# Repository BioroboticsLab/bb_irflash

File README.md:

# bb_irflash - Infrared LED flashing software and hardware

----
## What is bb_irflash?

bb_irflash is a software and hardware layout package. It contains the circuit and board layout for creating infrared flashing devices.

## Software

The software is C code written and tested for the Arduino Board Duemilanove. However, it should be easily adjusted to fit any arduino available on the market.

## Hardware

The hardware is designed to be triggered via signal current and powered with 12V. The design contains no protection mechanism whatsoever. So exchanging the resistors and/or LED's enables faster/slower flashing or constant lighting. 

The board dimensions are 23mmx51mm, single sided layout. Parts as described in the 'Parts' section enable flashing at 3 Hz and 20 ms duration. Designs come in EAGLE format.

# Parts

## SMD Parts Required for the Boards

The following Surface-Mount Device (SMD) parts are required for the boards:

### MOSFETs
- 8x [NTMS4807NR2G 'AO4752'](https://www.mouser.de/ProductDetail/863-NTMS4807NR2G)

### LEDs
- 8x [LED OSRAM 'SFH 4716AS A01'](https://www.mouser.de/ProductDetail/ams-OSRAM/SFH-4716AS-A01?qs=%252BEew9%252B0nqrDXvNyoSKrong%3D%3D)

### Signal Amplifiers
- 4x [Signal Amplifier 'LM358LVIDR'](https://www.mouser.de/ProductDetail/595-LM358LVIDR)

### Resistors
- 32x [2 Ohm Resistor '603-RC2512JK-072RL'](https://www.mouser.de/ProductDetail/603-RC2512JK-072RL)
- 16x [10k Ohm Resistor '71-CRCW060310K0JNEAC'](https://www.mouser.de/ProductDetail/71-CRCW060310K0JNEAC)
- 2x [4.7k Ohm Resistor '71-CRCW06034K70JNEAC'](https://www.mouser.de/ProductDetail/71-CRCW06034K70JNEAC)
- 4x [22k Ohm Resistor '71-CRCW060322K0JNEAC'](https://www.mouser.de/ProductDetail/71-CRCW060322K0JNEAC)
- 1x [20k Ohm Resistor 'R0603'](Beta Layout standard part) [20k Resistor on Mouser '71-CRCW060320K0JNEA'](https://www.mouser.de/ProductDetail/71-CRCW060320K0JNEAC)
)
- 1x [100k Ohm Resistor '71-CRCW0603100KFKEAC'](https://www.mouser.de/ProductDetail/71-CRCW0603100KFKEAC)

### Capacitors
- 4x [0.01uF Capacitor '810-C1005X7R1H103KBE'](https://www.mouser.de/ProductDetail/810-C1005X7R1H103KBE)
- 2x [1uF Capacitor '81-GRM155R61C105MA2D'](https://www.mouser.de/ProductDetail/81-GRM155R61C105MA2D)

### Diodes
- 2x [Schottky Diode 'CDBU0230R-HF'](https://www.mouser.de/ProductDetail/750-CDBU0230R-HF)

### Transistors
- 2x [NPN Transistor 'NSVMMBT2222AM3T5G'](https://www.mouser.de/ProductDetail/863-NSVMMBT2222AM3T5)

### Timer
- 2x [Timer 'NE555DR'](https://www.mouser.de/ProductDetail/595-NE555DR)

### Logic Gates
- 1x [Dual AND Gate '74LVC2G08'](https://www.mouser.de/ProductDetail/771-74LVC2G08DP-G)

## Through-hole-technology (THT) required components to solder on

### Capacitors
- 8x [2mF Capacitor '667-EEU-FP1E202B'](https://www.mouser.de/ProductDetail/667-EEU-FP1E202B)

### MOSFET
- 1x [STD12NF06L-1 'STD12NF06L-1'](https://www.mouser.de/ProductDetail/511-STD12NF06L-1)

### Connectors
- 8x [Header - Board to LED connections](https://www.mouser.de/ProductDetail/538-43045-0400)
- 1x [Header - Arduino connection](https://www.mouser.de/ProductDetail/538-105313-1203).  Note that the picture shows the incorrect part with number 1103.  The right angle connection
- 1x [Header - Power supply connection](https://www.mouser.de/ProductDetail/538-76825-0002)

See order_examples for further detail, and reference the picture for needed parts.  

# Mouser project order templates for parts:
- [bb_irflash SMD components Mouser project to order](https://eu.mouser.com/ProjectManager/ProjectDetail.aspx?AccessID=517e59b65d)
- [bb_irflash SMD components spreadsheet list](order_examples/BB_IRFLASH_SMD_COMPONENTS.xls)
- [bb_irflash THT components Mouser project to order](https://eu.mouser.com/ProjectManager/ProjectDetail.aspx?AccessID=0B309C354D)
- [bb_irflash THT components spreadsheet list](order_examples/BB_IRFLASH_THT_COMPONENTS.xls)
- [Cables for connecting lights, Arduino, and power supply](https://www.mouser.de/ProjectManager/ProjectDetail.aspx?AccessID=e691302b18). Note that the Arduino connection cable (Nanofit) and the power supply cable (Megafit) connect to the board, but will have to be cut/adjusted to make appropriate connections to the Arduino/power supply

# Power supply
The board is typically driven at 5V.  However, higher light output can be achieved by driving at slightly higher voltages.  here are suitable power supply for these voltages.  Note that when operating at 6fps and 5msec flashes, one board will draw 1-1.5 amps maximum.  Therefore one of these power supplies is sufficient to drive multiple boards.
- [5V power supply (adjustable in range 4.75-5.8V)](https://www.mouser.de/ProductDetail/MEAN-WELL/HRP-100-5?qs=Pc4kzEvJlcQLHIPhYtoJzw%3D%3D)
- [7.5V power supply (adjustable in range 6-9V)](https://www.mouser.de/ProductDetail/MEAN-WELL/RSP-320-7.5?qs=Uzd%2Fwh%252BZzhAvdwoq1II01Q%3D%3D).  Also available at [Conrad](https://www.conrad.de/de/p/mean-well-rsp-320-7-5-schaltnetzteil-7-5-v-dc-40-a-300-w-2249344.html?utm_source=google&utm_medium=cpc&utm_campaign=GB1_Messtechnik+%26+Stromversorgung_Generic&utm_id=43483581&gad_source=1&gbraid=0AAAAAD1-3H5RXiWIoMa0wxSd_K8oRlJKH&gclid=CjwKCAiAudG5BhAREiwAWMlSjDPmVMJK24BTLvHd9yjfUtIwc8q5r0EybappmSUyCZYAYHu7tNM5choC1wwQAvD_BwE&refresh=true)

# Board V2.0

The new IR flash board have the exact same performance as the previous version. The only new part is a better connectivity and a protection circuit.
The protection circuit is limiting the impulse duration to 20ms with a pause of 100ms between each pulse for protecting the LED. The power supply should be 
V ; 6A. To use it just send a step signal of the wanted duration to the trigger pin of the board (The step signal should not be wider than 20ms high and a pause of 100ms should be observe between each pulse)

The files in "board_V2" folder are all the project file in KiCAD format. If you have no interest in redesign, they are not interesting for you. 

For fabrication you only need the files in the fabrication folder.
The gerber files contained in "fabrication/gerber" are the map of your circuits - You manufacturer would ask for them (likely as a zip file, i.e. gerber.zip containing all folder contents).  The subfolder : "fabrication/gerber/drill_file" contain the coordinate of all the holes drilled into the board.

If you want to ask a third party for assembly, you will need the gerber files, the components position files ("Bestückungsplan": assembly_map_top.pdf
and assembly_map_bottom.pdf), the Pick&Place placement file (Pick&Place.txt), and the components list (Bill of Materials: BOM.xlsx). The 
The components position files are in component_position folder (Bottom and top layer). Note that the BOM format can vary in function of your third party company.

The folder order_examples contains two examples for orders placed through Beta Layout with components ordered through Mouser.  These are for reference.

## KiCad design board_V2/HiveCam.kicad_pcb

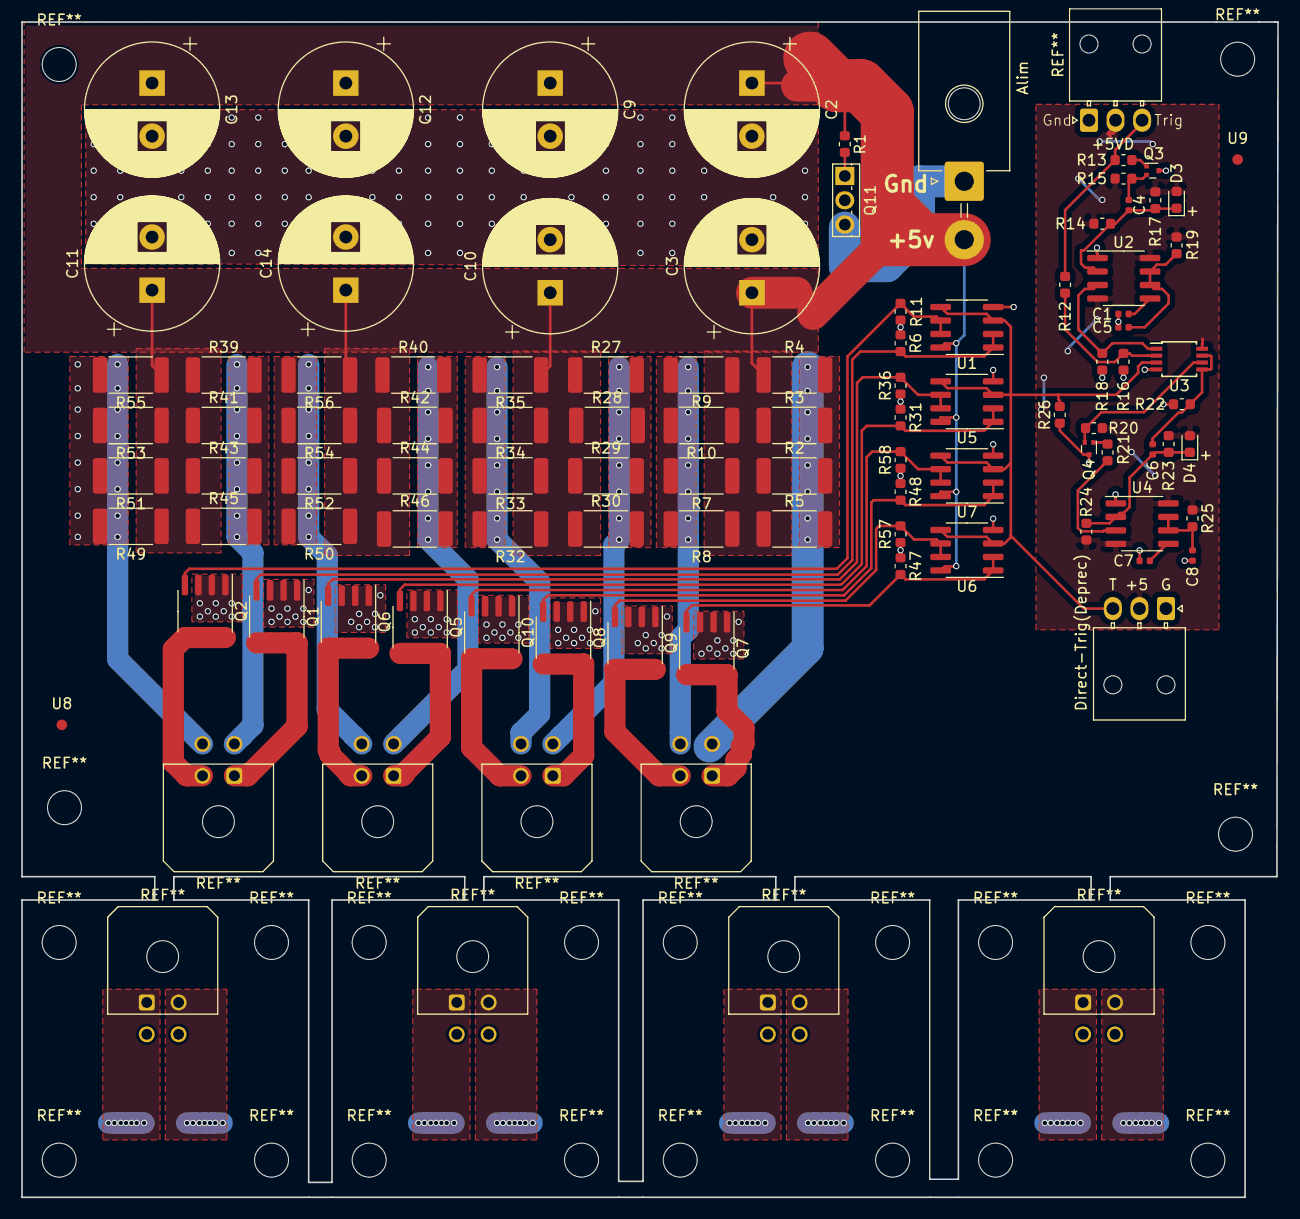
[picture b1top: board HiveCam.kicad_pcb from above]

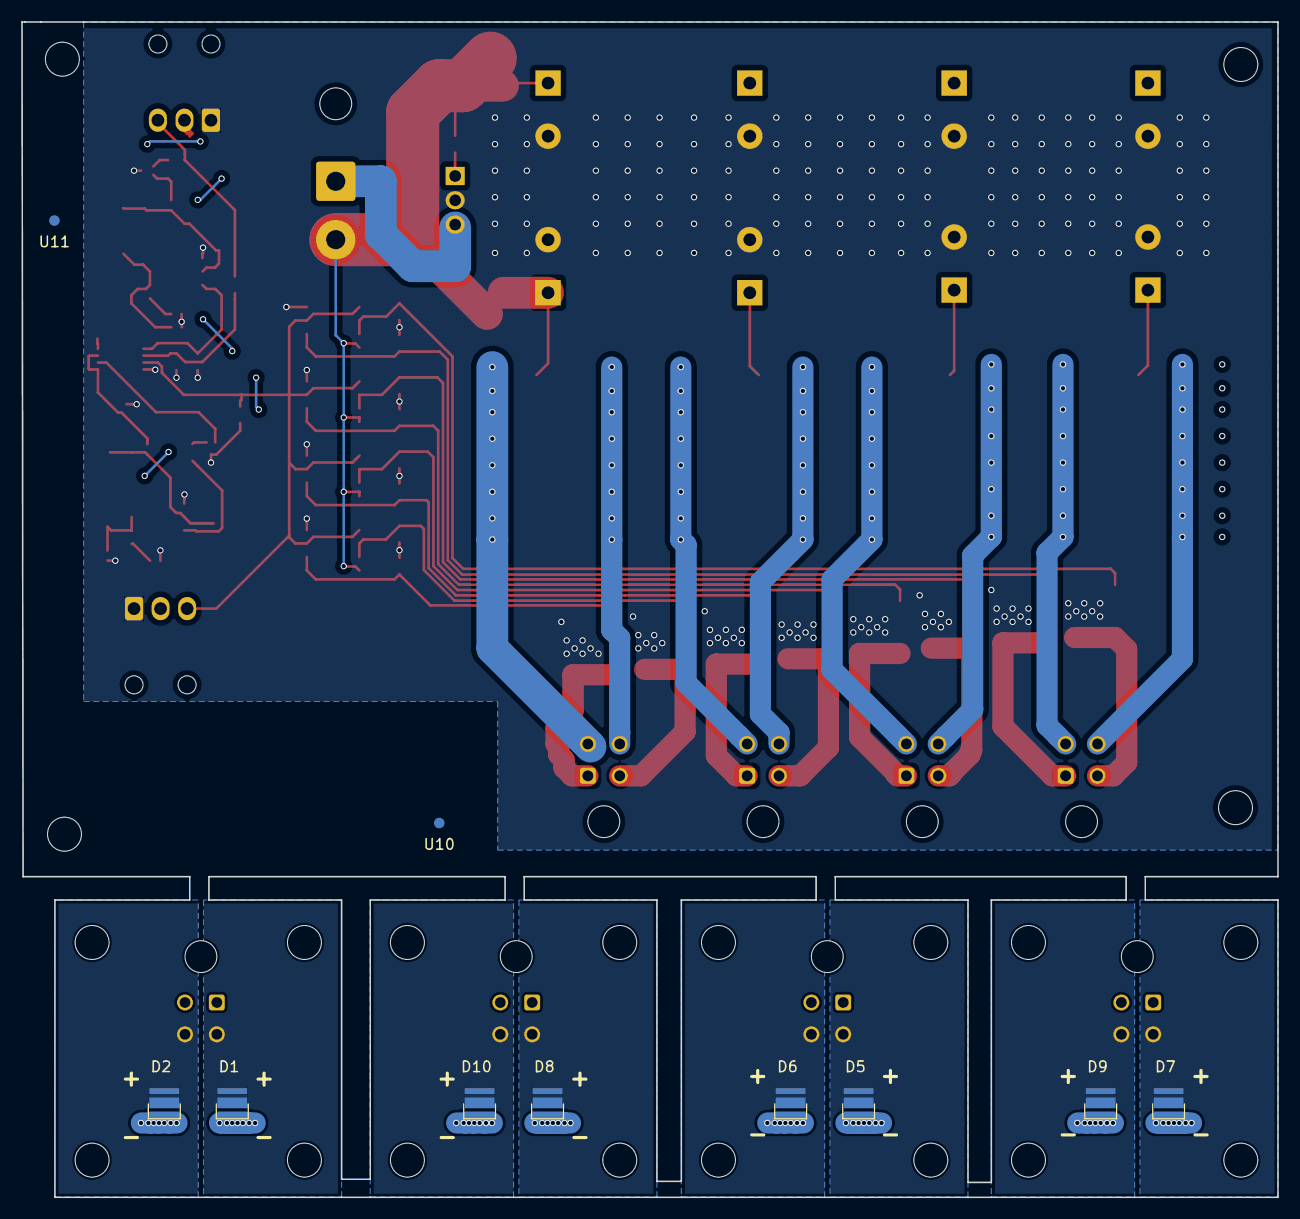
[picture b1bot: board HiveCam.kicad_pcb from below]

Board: 2 copper layers, 118.3 x 110.7 mm, 104 parts (10 on the bottom side), 39 nets.

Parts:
Alim: Molex_Mega-Fit_76825-0002_2x01_P5.70mm_Horizontal
C1, C4, C6, C7: 0.01u; C_0402_1005Metric
C2, C3, C9, C10, C11, C12, C13, C14: 2m; CP_Radial_D12.5mm_P5.00mm
C5, C8: 1u; C_0402_1005Metric
D1, D2, D5, D6, D7, D8, D9, D10: LED; SFH-4716S
D3, D4: DIODE; D_0603_1608Metric
Direct-Trig(Deprec): Molex_Nano-Fit_105313-xx03_1x03_P2.50mm_Horizontal
Q1, Q2, Q5, Q6, Q7, Q8, Q9, Q10: NTMS4807NR2G; SOIC-8_3.9x4.9mm_P1.27mm
Q3, Q4: NSVMMBT2222AM3T5G; SOT-723
Q11: RFD14N05L; TO-251-3_Vertical
R1, R6, R11, R12, R13, R16, R18, R21, R22, R26, R31, R36, R47, R48, R57, R58: 10k; R_0603_1608Metric
R2, R3, R4, R5, R7, R8, R9, R10, R27, R28, R29, R30, R32, R33, R34, R35, R39, R40, R41, R42, R43, R44, R45, R46, R49, R50, R51, R52, R53, R54, R55, R56: 2; R_2512_6332Metric
R14, R17, R23, R24: 22k; R_0603_1608Metric
R15, R20: 4.7k; R_0603_1608Metric
R19: 20k; R_0603_1608Metric
R25: 100k; R_0603_1608Metric
U1, U5, U6, U7: LMV358; SOIC-8_3.9x4.9mm_P1.27mm
U2, U4: NE555DR; SOIC-8_3.9x4.9mm_P1.27mm
U3: 74LVC2G08; TSSOP-8_3x3mm_P0.65mm
U8, U9, U10, U11: ref; Fiducial_1mm_Mask2mm

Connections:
+5V: Alim.2, C2.1, C3.1, C9.1, C10.1, C11.1, C12.1, C13.1, C14.1, R1.1, R2.1, R3.1, R4.1, R5.1, R7.1, R8.1, R9.1, R10.1, R27.1, R28.1, R29.1, R30.1, R32.1, R33.1, R34.1, R35.1, R39.1, R40.1, R41.1, R42.1, R43.1, R44.1, R45.1, R46.1, R49.1, R50.1, R51.1, R52.1, R53.1, R54.1, R55.1, R56.1, U1.8, U5.8, U6.8, U7.8
+5vD: D3.2, D4.2, Direct-Trig(Deprec).2, R14.2, R15.1, R17.1, R19.1, R20.1, R23.1, R24.2, R25.1, U2.4, U2.8, U3.8, U4.4, U4.8
GND: Alim.1, Q11.3
GNDP: C1.2, C2.2, C3.2, C5.2, C7.2, C8.2, C9.2, C10.2, C11.2, C12.2, C13.2, C14.2, Direct-Trig(Deprec).1, Q1.1, Q1.2, Q1.3, Q2.1, Q2.2, Q2.3, Q3.3, Q4.3, Q5.1, Q5.2, Q5.3, Q6.1, Q6.2, Q6.3, Q7.1, Q7.2, Q7.3, Q8.1, Q8.2, Q8.3, Q9.1, Q9.2, Q9.3, Q10.1, Q10.2, Q10.3, Q11.2, R6.1, R11.1, R16.1, R18.1, R22.1, R26.1, R31.1, R36.1, R47.1, R48.1, R57.1, R58.1, U1.4, U2.1, U3.4, U4.1, U5.4, U6.4, U7.4
unnamed: C1.1, U2.5
unnamed: C4.1, D3.1, R14.1, R17.2, U2.2
unnamed: C4.2, Q3.2, R15.2
unnamed: C5.1, R19.2, U2.6, U2.7
unnamed: C6.1, D4.1, R23.2, R24.1, U4.2
unnamed: C6.2, R22.2, U3.5, U3.7
unnamed: C7.1, U4.5
unnamed: C8.1, R25.2, U4.6, U4.7
unnamed: R2.2, R3.2, R4.2, R5.2
unnamed: R7.2, R8.2, R9.2, R10.2
unnamed: R27.2, R28.2, R29.2, R30.2
unnamed: R32.2, R33.2, R34.2, R35.2
unnamed: D1.1, D5.1, D7.1, D8.1, Q7.5
unnamed: D1.2, D5.2, D7.2, D8.2, R39.2, R41.2, R43.2, R45.2
unnamed: R40.2, R42.2, R44.2, R46.2
unnamed: D2.1, D6.1, D9.1, D10.1, Q9.5
unnamed: D2.2, D6.2, D9.2, D10.2, R49.2, R51.2, R53.2, R55.2
unnamed: R50.2, R52.2, R54.2, R56.2
unnamed: Q1.4, R6.2, U1.1, U1.2
unnamed: Q2.4, R11.2, U1.6, U1.7
unnamed: Q3.1, R13.1
unnamed: Q4.1, R21.1
unnamed: Q4.2, R20.2, U3.6
unnamed: Q5.4, R31.2, U5.1, U5.2
unnamed: Q6.4, R36.2, U5.6, U5.7
unnamed: Q7.4, R47.2, U6.1, U6.2
unnamed: Q8.4, R48.2, U7.1, U7.2
unnamed: Q9.4, R57.2, U6.6, U6.7
unnamed: Q10.4, R58.2, U7.6, U7.7
unnamed: Q11.1, R1.2
unnamed: R12.2, R16.2, U3.2
unnamed: R18.2, U2.3, U3.1
unnamed: R21.2, U4.3
unnamed: Direct-Trig(Deprec).3, R26.2, U1.3, U1.5, U3.3, U5.3, U5.5, U6.3, U6.5, U7.3, U7.5
Trigger: R12.1, R13.2

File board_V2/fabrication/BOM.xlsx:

BILL OF MATERIALS | GROUPED BY VALUES | AS OF 03.14.2024
Part | Value | Device | Package | Description | Description2 | Qty | Place_YES/NO | Provided_by_customer_YES/NO | Distributor | ItemNumber | Remarks
C1, C6, C7, C4, | 0.01u | C | Capacitor_SMD:C_0402_1005Metric | Unpolarized capacitor | Multilayer Ceramic Capacitors MLCC - SMD/SMT SOFT 0402 50V 0.01uF X7R 10% T: 0.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 | 4 | Y | N | Mouser | 810-C1005X7R1H103KBE | https://www.mouser.fr/ProductDetail/810-C1005X7R1H103KBE
C2, C3, C10, C9, C14, C12, C13, C11, | 2m | CP | Capacitor_THT:CP_Radial_D12.5mm_P5.00mm | Polarized capacitor | Aluminium Electrolytic Capacitors - Radial Leaded 25VDC 2000uF 20% ESR 0.030ohm | 8 | N | N | Mouser | 667-EEU-FP1E202B | https://www.mouser.fr/ProductDetail/667-EEU-FP1E202B
C5, C8, | 1u | C | Capacitor_SMD:C_0402_1005Metric | Unpolarized capacitor | Multilayer Ceramic Capacitors MLCC - SMD/SMT 0402 1uF 16volts X5R 20% | 2 | Y | N | Mouser | 81-GRM155R61C105MA2D | https://www.mouser.fr/ProductDetail/81-GRM155R61C105MA2D
D2, D1, D5, D6, D8, D10, D7, D9, | LED | LED | LED:SFH 4716AS A01 | Light emitting diode | Infrared Emitters - High Power Infrared 850 nm | 8 | Y | N | Mouser | 720-SFH4716ASAA5051 | https://www.mouser.de/ProductDetail/ams-OSRAM/SFH-4716AS-A01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
D3, D4, | CDBU0230R-HF | CDBU0230R-HF | Diode_SMD:D_0603_1608Metric | Diode | Schottky Diodes & Rectifiers VR=30V, IO=200mA | 2 | Y | N | Mouser | 750-CDBU0230R-HF | https://www.mouser.fr/ProductDetail/750-CDBU0230R-HF
Q2, Q1, Q5, Q6, Q8, Q10, Q7, Q9, | NTMS4807NR2G | AO4752 | Package_SO:SOIC-8_3.9x4.9mm_P1.27mm |  |  | 8 | Y | N | Mouser | 863-NTMS4807NR2G | https://www.mouser.fr/ProductDetail/863-NTMS4807NR2G
Q3, Q4, | NSVMMBT2222AM3T5G | Q_NPN_BCE | Package_TO_SOT_SMD:SOT-723 | NPN transistor, base/collector/emitter | Bipolar Transistors - BJT SS SOT-723 GP TRANSISTOR | 2 | Y | N | Mouser | 863-NSVMMBT2222AM3T5 | https://www.mouser.fr/ProductDetail/863-NSVMMBT2222AM3T5
Q11, | STD12NF06L-1 | STD12NF06L-1 | Package_TO_SOT_THT:TO-251-3_Vertical | 50V Vds, 0.22A Id, N-Channel MOSFET, SOT-23 | MOSFET TO-251AA N-Ch Power | 1 | N | N | Mouser | 511-STD12NF06L-1 | https://www.mouser.de/ProductDetail/511-STD12NF06L-1
R3, R4, R10, R9, R8, R2, R7, R5, R32, R27, R33, R34, R35, R30, R29, R28, R50, R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 | 2 | R | Resistor_SMD:R_2512_6332Metric | Resistor | Thick Film Resistors - SMD 2 OHM 5% | 32 | Y | N | Mouser | 603-RC2512JK-072RL | https://www.mouser.fr/ProductDetail/603-RC2512JK-072RL
R13, R12, R18, R16, R21, R22, R11, R6, R31, R36, R48, R58, R47, R57, R26, R1, | 10k | R | Resistor_SMD:R_0603_1608Metric | Resistor | Thick Film Resistors - SMD 1/10Watt 10Kohms 5% Commercial Use | 16 | Y | N | Mouser | 71-CRCW060310K0JNEAC | https://www.mouser.fr/ProductDetail/71-CRCW060310K0JNEAC
R15, R20, | 4.7k | R | Resistor_SMD:R_0603_1608Metric | Resistor | Thick Film Resistors - SMD 1/10Watt 4.7Kohms 5% Commercial Use | 2 | Y | N | Mouser | 71-CRCW06034K70JNEAC | https://www.mouser.fr/ProductDetail/71-CRCW06034K70JNEAC
R17, R14, R23, R24, | 22k | R | Resistor_SMD:R_0603_1608Metric | Resistor | Thick Film Resistors - SMD 1/10Watt 22Kohms 5% Commercial Use | 4 | Y | N | Mouser | 71-CRCW060322K0JNEAC | https://www.mouser.fr/ProductDetail/71-CRCW060322K0JNEAC
R19, | 20k | R0603 | Resistor_SMD:R_0603_1608Metric | Resistor |  | 1 | Y | N | Beta | R0603
R25, | 100k | R | Resistor_SMD:R_0603_1608Metric | Resistor | Thick Film Resistors - SMD 1/10Watt 100Kohms 1% Commercial Use | 1 | Y | N | Mouser | 71-CRCW0603100KFKEAC | https://www.mouser.fr/ProductDetail/71-CRCW0603100KFKEAC
U1, U5, U7, U6, | LMV358 | LMV358 | Package_SO:SOIC-8_3.9x4.9mm_P1.27mm | Dual Low-Voltage Rail-to-Rail Output Operational Amplifiers, SOIC-8/SSOP-8 | Operational Amplifiers - Op Amps Low Cost RRO amp General Purpose Dual | 4 | Y | N | Mouser | 595-LM358LVIDR | https://www.mouser.de/ProductDetail/Texas-Instruments/LM358L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
U2, U4, | NE555DR | LM555 | Package_SO:SOIC-8_3.9x4.9mm_P1.27mm | Timer, DIP-8/SOIC-8/SSOP-8 | Timers & Support Products Precision | 2 | Y | N | Mouser | 595-NE555DR | https://www.mouser.fr/ProductDetail/595-NE555DR
U3, | 74LVC2G08 | 74LVC2G08 | Package_SO:TSSOP-8_3x3mm_P0.65mm | Dual AND Gate, Low-Voltage CMOS |  | 1 | Y | N | Mouser | 771-74LVC2G08DP-G | https://www.mouser.fr/ProductDetail/771-74LVC2G08DP-G

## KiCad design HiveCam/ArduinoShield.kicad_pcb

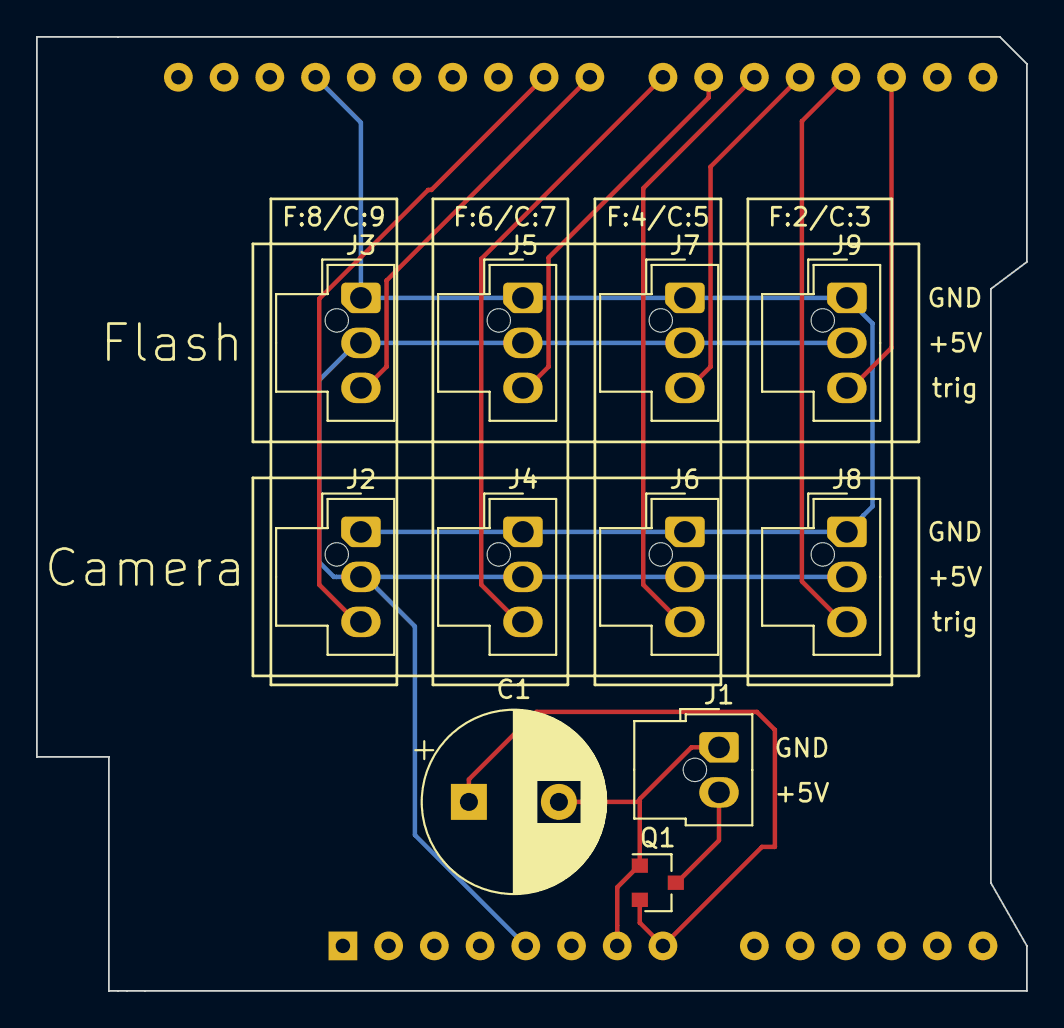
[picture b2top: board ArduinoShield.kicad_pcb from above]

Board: 2 copper layers, 55.0 x 53.0 mm, 12 parts (1 on the bottom side), 13 nets.

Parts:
A1: Arduino_UNO_R3
C1: EEU-TP1E511B; CP_Radial_D10.0mm_P5.00mm
J1: Conn_01x02; Molex_Nano-Fit_105309-xx02_1x02_P2.50mm_Vertical
J2, J3, J4, J5, J6, J7, J8, J9: Conn_01x03; Molex_Nano-Fit_105309-xx03_1x03_P2.50mm_Vertical
Q1: NTR1P02T1G; SOT-23

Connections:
unnamed: A1.7, C1.2, J1.1, Q1.1
unnamed: A1.8, C1.1, Q1.2
unnamed: A1.17, J9.3
unnamed: A1.18, J8.3
unnamed: A1.19, J7.3
unnamed: A1.20, J6.3
unnamed: A1.21, J5.3
unnamed: A1.22, J4.3
unnamed: A1.23, J3.3
unnamed: A1.24, J2.3
unnamed: A1.29, J2.1, J3.1, J4.1, J5.1, J6.1, J7.1, J8.1, J9.1
unnamed: J1.2, Q1.3
unnamed: A1.5, J2.2, J3.2, J4.2, J5.2, J6.2, J7.2, J8.2, J9.2

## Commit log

2019-07-24 added original files scavenged from some old PC
2019-07-24 added coded modified on 2018 with more accurate delays and less jitter
2019-07-24 increased time between frames a little
2020-02-12 added simultaneous trigger added folder structure for different firmware variants
2020-02-14 Adding V2 board
2020-02-18 fixed bug in ms / us waiting time calculation
2020-02-18 completing README
2024-03-20 updated part numbers, cleaned up contents, added order examples
    Note: removed 'HiveCam' folder, because its contents were the same as board_v2. Moved PDFs with order details to separate folder, updated component links to Mouser, and included updated bill of mater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
2024-08-29 Create LICENSE
2024-11-12 added xls Mouser component lists
2025-02-06 update variable name
2025-02-20 Add 3D enclosure model files
2026-04-16 mosfet corrected to tht version
2026-04-16 add order including THT components
2026-04-22 replace mosfet due to end-of-life for other part
